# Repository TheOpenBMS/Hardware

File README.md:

# Hardware
KiCad Schematics and PCB Layout

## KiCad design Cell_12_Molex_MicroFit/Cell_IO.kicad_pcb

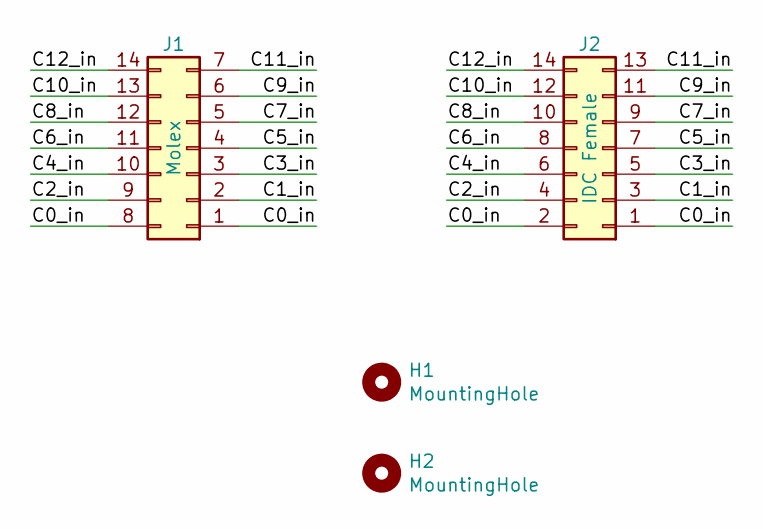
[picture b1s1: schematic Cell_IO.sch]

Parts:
H1, H2: MountingHole; MountingHole_3.2mm_M3
J1: Molex; Molex_Micro-Fit_3.0_43045-1400_2x07_P3.00mm_Horizontal
J2: IDC Female; PinSocket_2x07_P2.54mm_Horizontal

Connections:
/C0_in: J1.1, J1.8, J2.1, J2.2
/C1_in: J1.2, J2.3
/C2_in: J1.9, J2.4
/C3_in: J1.3, J2.5
/C4_in: J1.10, J2.6
/C5_in: J1.4, J2.7
/C6_in: J1.11, J2.8
/C7_in: J1.5, J2.9
/C8_in: J1.12, J2.10
/C9_in: J1.6, J2.11
/C10_in: J1.13, J2.12
/C11_in: J1.7, J2.13
/C12_in: J1.14, J2.14

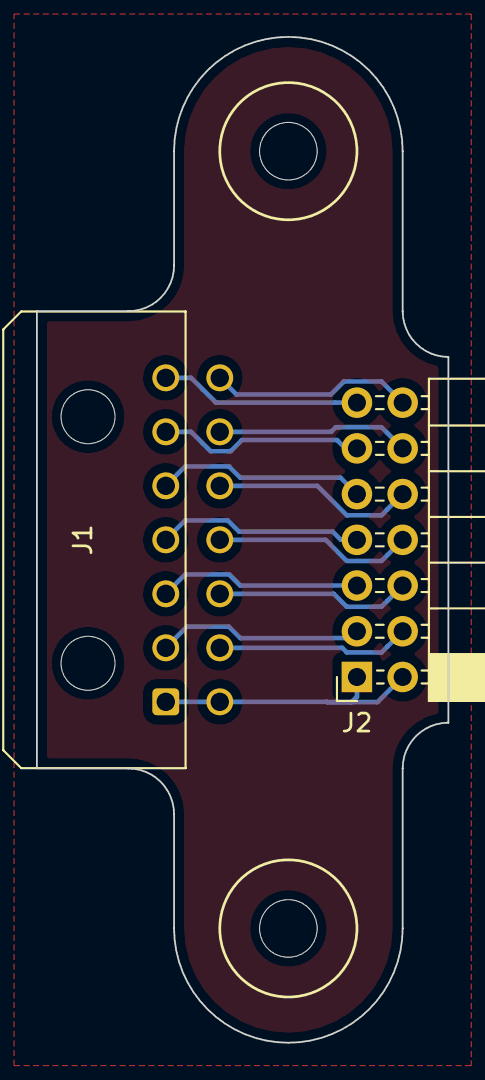
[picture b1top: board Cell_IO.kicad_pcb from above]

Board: 2 copper layers, 22.9 x 55.9 mm, 4 parts (0 on the bottom side), 13 nets.

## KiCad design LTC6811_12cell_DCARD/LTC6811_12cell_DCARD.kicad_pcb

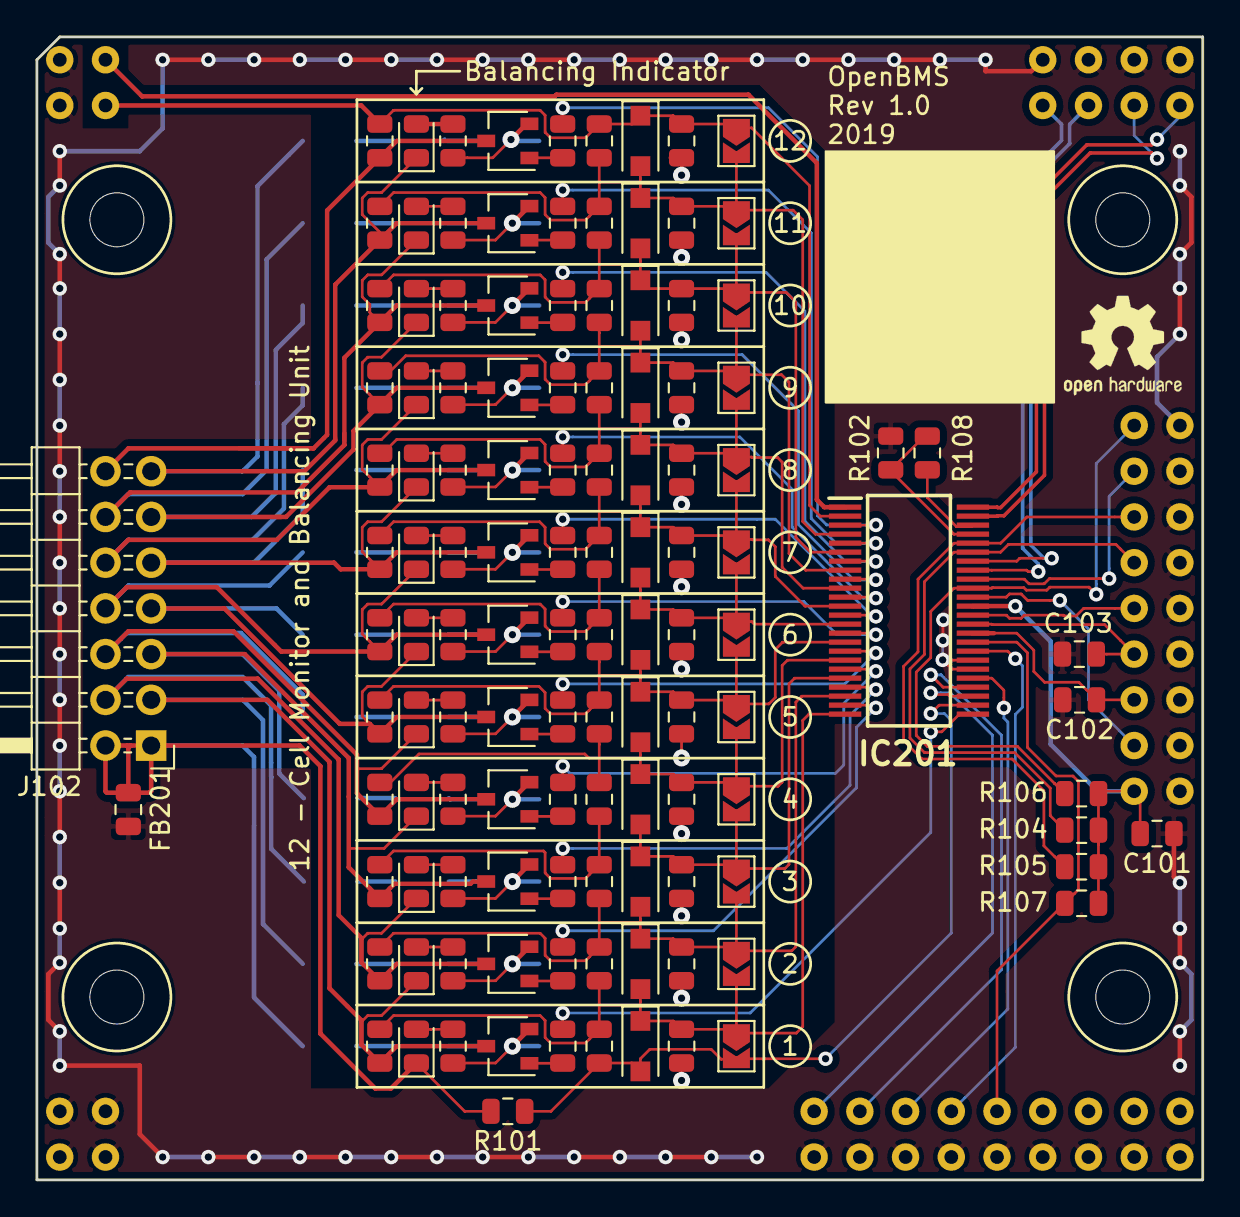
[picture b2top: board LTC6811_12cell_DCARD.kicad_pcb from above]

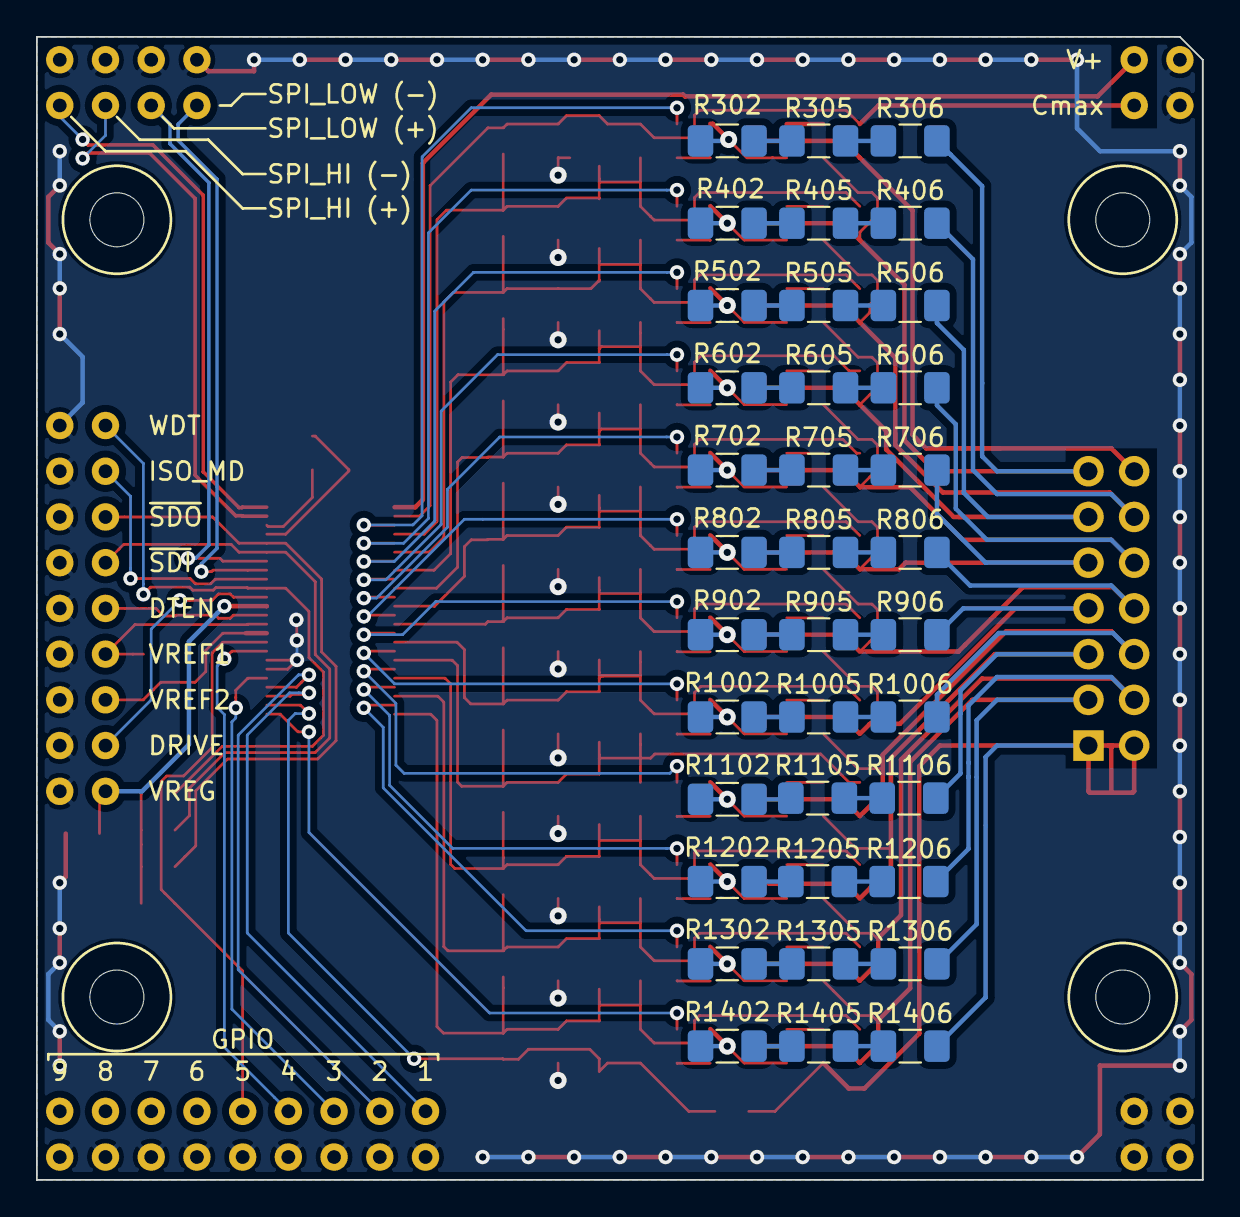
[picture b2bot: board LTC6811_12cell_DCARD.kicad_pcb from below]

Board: 2 copper layers, 64.8 x 63.5 mm, 158 parts (36 on the bottom side), 120 nets.

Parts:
C101, C102, C103: 1u; C_0805_2012Metric
C301, C401, C501, C601, C701, C801, C901, C1001, C1101, C1201, C1301, C1401: 100n; C_0805_2012Metric
C302, C402, C502, C602, C702, C802, C902, C1002, C1102, C1202, C1302, C1402: 10n; C_0805_2012Metric
D301, D401, D501, D601, D701, D801, D901, D1001, D1101, D1201, D1301, D1401: LED; LED_0805_2012Metric
D302, D402, D502, D602, D702, D802, D902, D1002, D1102, D1202, D1302, D1402: BAT46W; D_SOD-123F
FB201: Ferrite_Bead; R_0805_2012Metric
IC201: LTC6811-1; SOP50P780X200-48N
J102: Cells_1-12; PinHeader_2x07_P2.54mm_Horizontal
JP301, JP401, JP501, JP601, JP701, JP801, JP901, JP1001, JP1101, JP1201, JP1301, JP1401: Cell_Bypass; SolderJumper-2_P1.3mm_Open_TrianglePad1.0x1.5mm
Q301, Q401, Q501, Q601, Q701, Q801, Q901, Q1001, Q1101, Q1201, Q1301, Q1401: BSS308PE; SOT-23W
R101, R303, R403, R503, R603, R703, R803, R903, R1003, R1103, R1203, R1303, R1403: 100; R_0805_2012Metric
R102, R108: 1k; R_0805_2012Metric
R104, R105, R106, R107: 1M; R_0805_2012Metric
R301, R401, R501, R601, R701, R801, R901, R1001, R1101, R1201, R1301, R1401: 475; R_0805_2012Metric
R302, R305, R306, R402, R405, R406, R502, R505, R506, R602, R605, R606, R702, R705, R706, R802, R805, R806, R902, R905, R906, R1002, R1005, R1006, R1102, R1105, R1106, R1202, R1205, R1206, R1302, R1305, R1306, R1402, R1405, R1406: 11; R_1206_3216Metric_Pad1.42x1.75mm_HandSolder
R304, R404, R504, R604, R704, R804, R904, R1004, R1104, R1204, R1304, R1404: 3.3k; R_0805_2012Metric
SHD201: OpenBMS_IO

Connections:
/C0: C1402.2, D1402.2, IC201.26, JP1401.2, R101.1
/C0_in: D1401.1, FB201.1, J102.1, J102.2, R101.2, R1406.2
/C1: C1302.2, C1401.1, C1402.1, D1302.2, D1402.1, IC201.24, JP1301.2, JP1401.1, R1403.1
/C1_in: D1301.1, J102.3, Q1401.3, R1306.2, R1403.2
/C2: C1202.2, C1301.1, C1302.1, D1202.2, D1302.1, IC201.22, JP1201.2, JP1301.1, R1303.1
/C2_in: D1201.1, J102.4, Q1301.3, R1206.2, R1303.2
/C3: C1102.2, C1201.1, C1202.1, D1102.2, D1202.1, IC201.20, JP1101.2, JP1201.1, R1203.1
/C3_in: D1101.1, J102.5, Q1201.3, R1106.2, R1203.2
/C4: C1002.2, C1101.1, C1102.1, D1002.2, D1102.1, IC201.18, JP1001.2, JP1101.1, R1103.1
/C4_in: D1001.1, J102.6, Q1101.3, R1006.2, R1103.2
/C5: C902.2, C1001.1, C1002.1, D902.2, D1002.1, IC201.16, JP901.2, JP1001.1, R1003.1
/C5_in: D901.1, J102.7, Q1001.3, R906.2, R1003.2
/C6: C802.2, C901.1, C902.1, D802.2, D902.1, IC201.14, JP801.2, JP901.1, R903.1
/C6_in: D801.1, J102.8, Q901.3, R806.2, R903.2
/C7: C702.2, C801.1, C802.1, D702.2, D802.1, IC201.12, JP701.2, JP801.1, R803.1
/C7_in: D701.1, J102.9, Q801.3, R706.2, R803.2
/C8: C602.2, C701.1, C702.1, D602.2, D702.1, IC201.10, JP601.2, JP701.1, R703.1
/C8_in: D601.1, J102.10, Q701.3, R606.2, R703.2
/C9: C502.2, C601.1, C602.1, D502.2, D602.1, IC201.8, JP501.2, JP601.1, R603.1
/C9_in: D501.1, J102.11, Q601.3, R506.2, R603.2
/C10: C402.2, C501.1, C502.1, D402.2, D502.1, IC201.6, JP401.2, JP501.1, R503.1
/C10_in: D401.1, J102.12, Q501.3, R406.2, R503.2
/C11: C302.2, C401.1, C402.1, D302.2, D402.1, IC201.4, JP301.2, JP401.1, R403.1
/C11_in: D301.1, J102.13, Q401.3, R306.2, R403.2
/C12: C301.1, C302.1, D302.1, IC201.2, JP301.1, R303.1, SHD201.Cmax_in
/C12_in: J102.14, Q301.3, R303.2
/DRIVE: IC201.38, SHD201.DRIVE
/DTEN: IC201.36, SHD201.DTEN
/GPIO1: IC201.27, SHD201.GPIO1
/GPIO2: IC201.28, SHD201.GPIO2
/GPIO3: IC201.29, SHD201.GPIO3
/GPIO4: IC201.32, SHD201.GPIO4
/GPIO5: IC201.33, R107.1, SHD201.GPIO5
/IBIAS: IC201.45, R102.2, R108.1
/ICMP: IC201.46, R108.2
/IH+: IC201.48, SHD201.IHP
/IH-: IC201.47, SHD201.IHM
/IL+: IC201.42, SHD201.ILP
/IL-: IC201.41, SHD201.ILM
/ISOMD: IC201.40, SHD201.ISOMD
/S1: IC201.25, R1404.1
/S2: IC201.23, R1304.1
/S3: IC201.21, R1204.1
/S4: IC201.19, R1104.1
/S5: IC201.17, R1004.1
/S6: IC201.15, R904.1
/S7: IC201.13, R804.1
/S8: IC201.11, R704.1
/S9: IC201.9, R604.1
/S10: IC201.7, R504.1
/S11: IC201.5, R404.1
/S12: IC201.3, R304.1
/V+: IC201.1, SHD201.V+
/VREF1: C103.1, IC201.35, SHD201.VREF1
/VREF2: C102.1, IC201.34, SHD201.VREF2
/VREG: C101.1, IC201.37, R104.2, R105.2, R106.2, R107.2, SHD201.VREG
/WDT: IC201.39, R106.1, SHD201.WDT
/~SDI: IC201.43, R104.1, SHD201.~SDI
/~SDO: IC201.44, R105.1, SHD201.~SDO
GND: C101.2, C102.2, C103.2, C301.2, C401.2, C501.2, C601.2, C701.2, C801.2, C901.2, C1001.2, C1101.2, C1201.2, C1301.2, C1401.2, FB201.2, IC201.30, IC201.31, R102.1, SHD201.GND
unnamed: D301.2, R301.2
unnamed: D401.2, R401.2
unnamed: D501.2, R501.2
unnamed: D601.2, R601.2
unnamed: D701.2, R701.2
unnamed: D801.2, R801.2
unnamed: D901.2, R901.2
unnamed: D1001.2, R1001.2
unnamed: D1101.2, R1101.2
unnamed: D1201.2, R1201.2
unnamed: D1301.2, R1301.2
unnamed: D1401.2, R1401.2
unnamed: Q301.1, R304.2
unnamed: Q301.2, R301.1, R302.1
unnamed: Q401.1, R404.2
unnamed: Q401.2, R401.1, R402.1
unnamed: Q501.1, R504.2
unnamed: Q501.2, R501.1, R502.1
unnamed: Q601.1, R604.2
unnamed: Q601.2, R601.1, R602.1
unnamed: Q701.1, R704.2
unnamed: Q701.2, R701.1, R702.1
unnamed: Q801.1, R804.2
unnamed: Q801.2, R801.1, R802.1
unnamed: Q901.1, R904.2
unnamed: Q901.2, R901.1, R902.1
unnamed: Q1001.1, R1004.2
unnamed: Q1001.2, R1001.1, R1002.1
unnamed: Q1101.1, R1104.2
unnamed: Q1101.2, R1101.1, R1102.1
unnamed: Q1201.1, R1204.2
unnamed: Q1201.2, R1201.1, R1202.1
unnamed: Q1301.1, R1304.2
unnamed: Q1301.2, R1301.1, R1302.1
unnamed: Q1401.1, R1404.2
unnamed: Q1401.2, R1401.1, R1402.1
unnamed: R302.2, R305.1
unnamed: R305.2, R306.1
unnamed: R402.2, R405.1
unnamed: R405.2, R406.1
unnamed: R502.2, R505.1
unnamed: R505.2, R506.1
unnamed: R602.2, R605.1
unnamed: R605.2, R606.1
unnamed: R702.2, R705.1
unnamed: R705.2, R706.1
unnamed: R802.2, R805.1
unnamed: R805.2, R806.1
unnamed: R902.2, R905.1
unnamed: R905.2, R906.1
unnamed: R1002.2, R1005.1
unnamed: R1005.2, R1006.1
unnamed: R1102.2, R1105.1
unnamed: R1105.2, R1106.1
unnamed: R1202.2, R1205.1
unnamed: R1205.2, R1206.1
unnamed: R1302.2, R1305.1
unnamed: R1305.2, R1306.1
unnamed: R1402.2, R1405.1
unnamed: R1405.2, R1406.1

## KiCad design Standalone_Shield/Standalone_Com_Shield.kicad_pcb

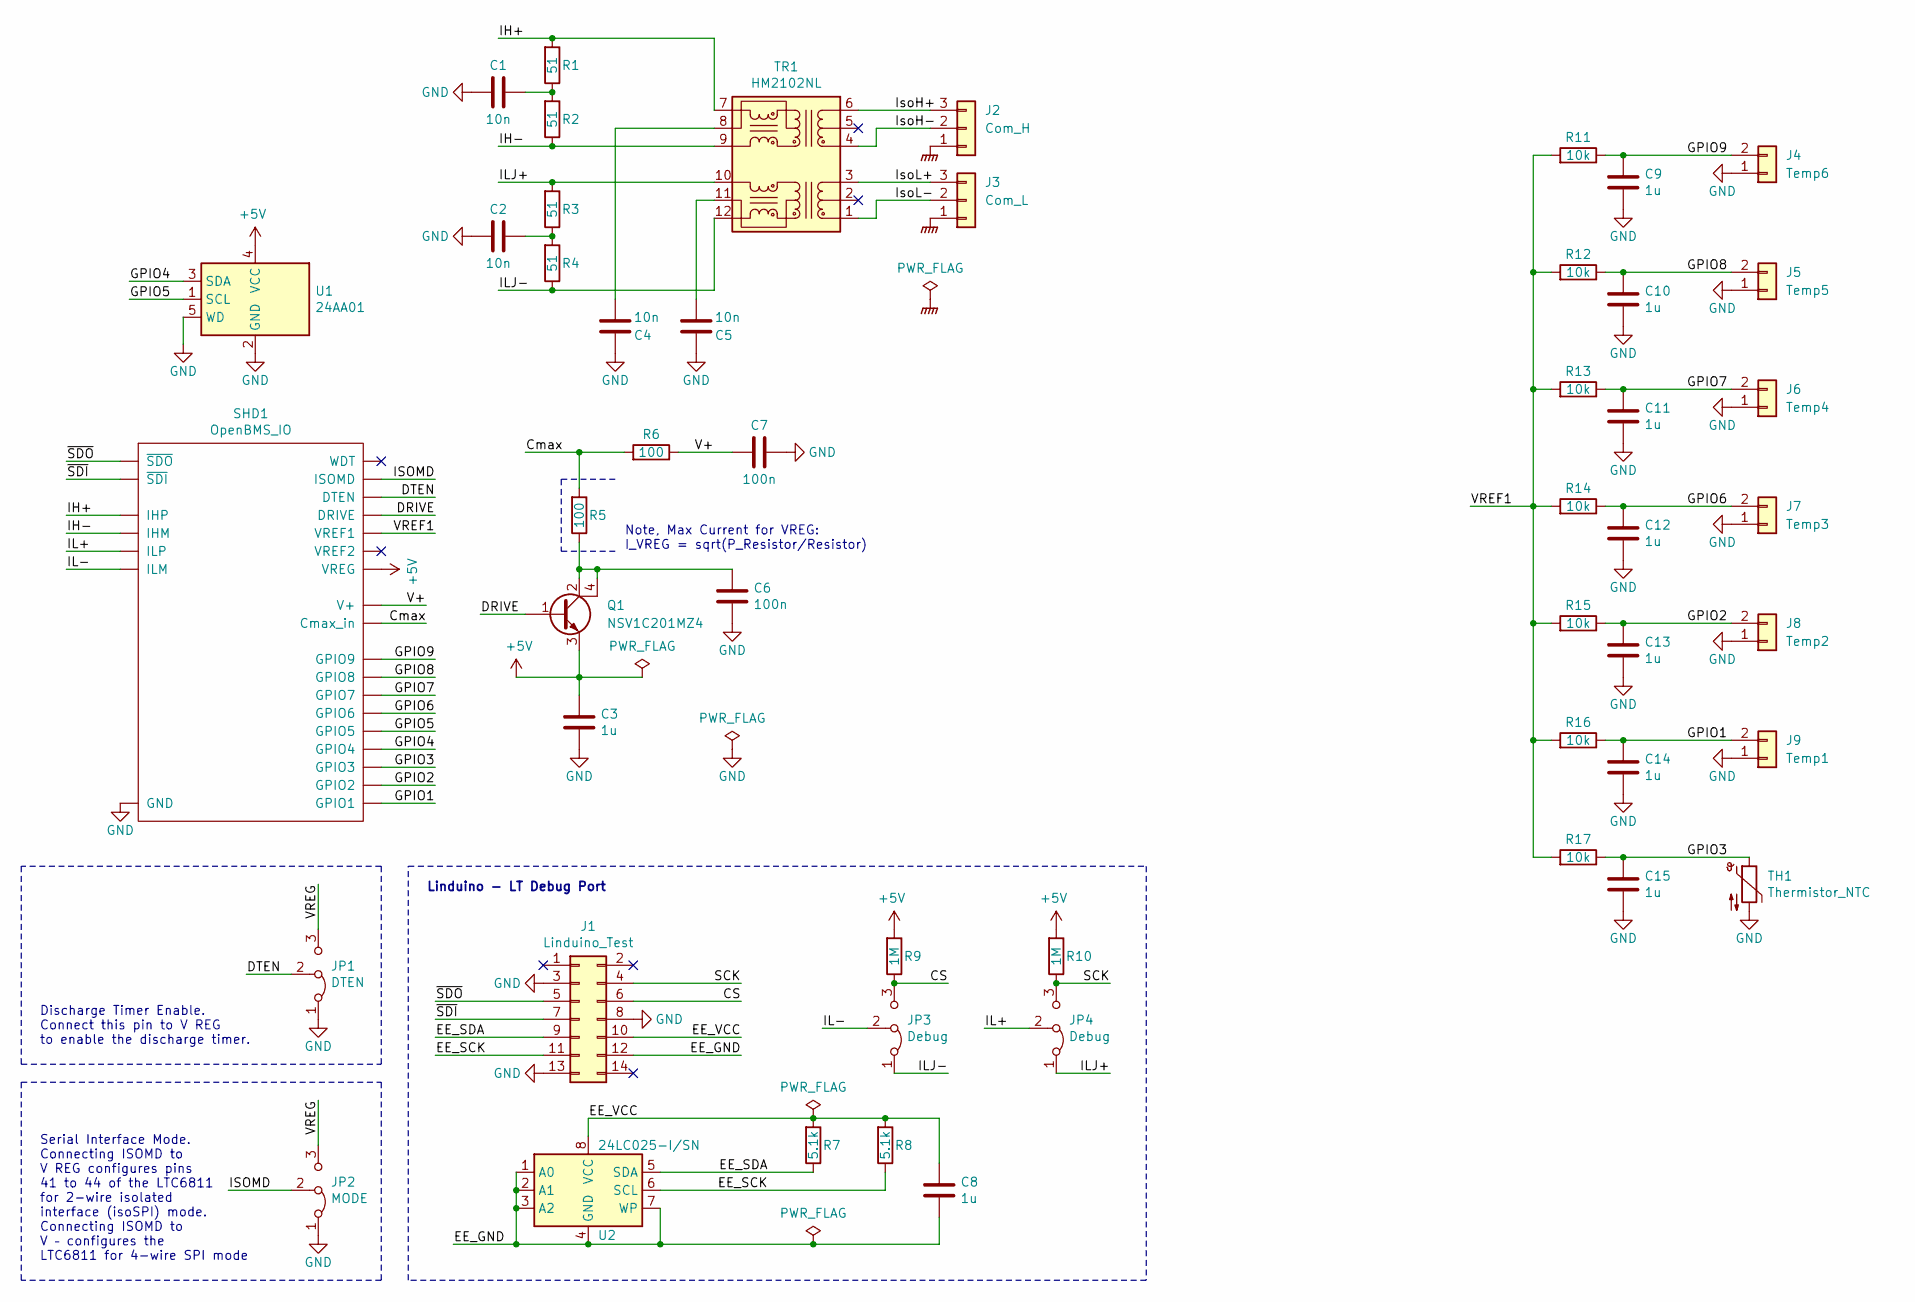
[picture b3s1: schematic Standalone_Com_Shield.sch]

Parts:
C1, C2, C4, C5: 10n; C_0805_2012Metric
C3, C8, C9, C10, C11, C12, C13, C14, C15: 1u; C_0805_2012Metric
C6, C7: 100n; C_0805_2012Metric
J1: Linduino_Test; IDC-Header_2x07_P2.54mm_Vertical
J2: Com_H; JST_XH_S03B-XH-A_1x03_P2.50mm_Horizontal
J3: Com_L; JST_XH_S03B-XH-A_1x03_P2.50mm_Horizontal
J4: Temp6; JST_PH_B2B-PH-SM4-TB_1x02-1MP_P2.00mm_Vertical
J5: Temp5; JST_PH_B2B-PH-SM4-TB_1x02-1MP_P2.00mm_Vertical
J6: Temp4; JST_PH_B2B-PH-SM4-TB_1x02-1MP_P2.00mm_Vertical
J7: Temp3; JST_PH_B2B-PH-SM4-TB_1x02-1MP_P2.00mm_Vertical
J8: Temp2; JST_PH_B2B-PH-SM4-TB_1x02-1MP_P2.00mm_Vertical
J9: Temp1; JST_PH_B2B-PH-SM4-TB_1x02-1MP_P2.00mm_Vertical
JP1: DTEN; PinHeader_1x03_P2.54mm_Horizontal
JP2: MODE; PinHeader_1x03_P2.54mm_Horizontal
JP3, JP4: Debug; PinHeader_1x03_P2.54mm_Horizontal
Q1: NSV1C201MZ4; SOT-223
R1, R2, R3, R4: 51; R_0805_2012Metric
R5, R6: 100; R_0805_2012Metric
R7, R8: 5.1k; R_0805_2012Metric
R9, R10: 1M; R_0805_2012Metric
R11, R12, R13, R14, R15, R16, R17: 10k; R_0805_2012Metric
SHD1: OpenBMS_IO
TH1: Thermistor_NTC; R_0603_1608Metric
TR1: HM2102NL
U1: 24AA01; SOT-23-5
U2: 24LC025-I/SN; SOIC-8_3.9x4.9mm_P1.27mm

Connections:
+5V: C3.1, Q1.3 (E), R9.2, R10.2, SHD1.VREG, U1.4 (VCC)
/CS: J1.6, JP3.3 (B), R9.1
/Cmax: R5.2, R6.2, SHD1.Cmax_in
/DRIVE: Q1.1 (B), SHD1.DRIVE
/DTEN: JP1.2 (C), SHD1.DTEN
/EE_GND: C8.2, J1.12, U2.1 (A0), U2.2 (A1), U2.3 (A2), U2.4 (GND), U2.7 (WP)
/EE_SCK: J1.11, R8.1, U2.6 (SCL)
/EE_SDA: J1.9, R7.1, U2.5 (SDA)
/EE_VCC: C8.1, J1.10, R7.2, R8.2, U2.8 (VCC)
/GPIO1: C14.1, J9.2, R16.1, SHD1.GPIO1
/GPIO2: C13.1, J8.2, R15.1, SHD1.GPIO2
/GPIO3: C15.1, R17.1, SHD1.GPIO3, TH1.1
/GPIO4: SHD1.GPIO4, U1.3 (SDA)
/GPIO5: SHD1.GPIO5, U1.1 (SCL)
/GPIO6: C12.1, J7.2, R14.1, SHD1.GPIO6
/GPIO7: C11.1, J6.2, R13.1, SHD1.GPIO7
/GPIO8: C10.1, J5.2, R12.1, SHD1.GPIO8
/GPIO9: C9.1, J4.2, R11.1, SHD1.GPIO9
/IH+: R1.2, SHD1.IHP, TR1.7 (RX-)
/IH-: R2.1, SHD1.IHM, TR1.9 (RX+)
/IL+: JP4.2 (C), SHD1.ILP
/IL-: JP3.2 (C), SHD1.ILM
/ILJ+: JP4.1 (A), R3.2, TR1.10 (TX-)
/ILJ-: JP3.1 (A), R4.1, TR1.12 (TX+)
/ISOMD: JP2.2 (C), SHD1.ISOMD
/IsoH+: J2.3, TR1.6 (RD-)
/IsoH-: J2.2, TR1.4 (RD+)
/IsoL+: J3.3, TR1.3 (TD-)
/IsoL-: J3.2, TR1.1 (TD+)
/SCK: J1.4, JP4.3 (B), R10.1
/V+: C7.1, R6.1, SHD1.V+
/VREF1: R11.2, R12.2, R13.2, R14.2, R15.2, R16.2, R17.2, SHD1.VREF1
/VREG: JP1.3 (B), JP2.3 (B)
/~SDI: J1.7, SHD1.~SDI
/~SDO: J1.5, SHD1.~SDO
GND: C1.2, C2.2, C3.2, C4.2, C5.2, C6.2, C7.2, C9.2, C10.2, C11.2, C12.2, C13.2, C14.2, C15.2, J1.3, J1.8, J1.13, J4.1, J5.1, J6.1, J7.1, J8.1, J9.1, JP1.1 (A), JP2.1 (A), SHD1.GND, TH1.2, U1.2 (GND), U1.5 (WD)
GNDPWR: J2.1, J3.1
unnamed: C1.1, R1.1, R2.2
unnamed: C2.1, R3.1, R4.2
unnamed: C4.1, TR1.8 (C_RX)
unnamed: C5.1, TR1.11 (C_TX)
unnamed: C6.1, Q1.2 (C), Q1.4 (C), R5.1

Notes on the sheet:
Note, Max Current for VREG: I_VREG = sqrt(P_Resistor/Resistor)
Serial Interface Mode. Connecting ISOMD to V REG configures pins 41 to 44 of the LTC6811 for 2-wire isolated interface (isoSPI) mode. Connecting ISOMD to V – configures the LTC6811 for 4-wire SPI mode
Discharge Timer Enable. Connect this pin to V REG to enable the discharge timer.
Linduino - LT Debug Port

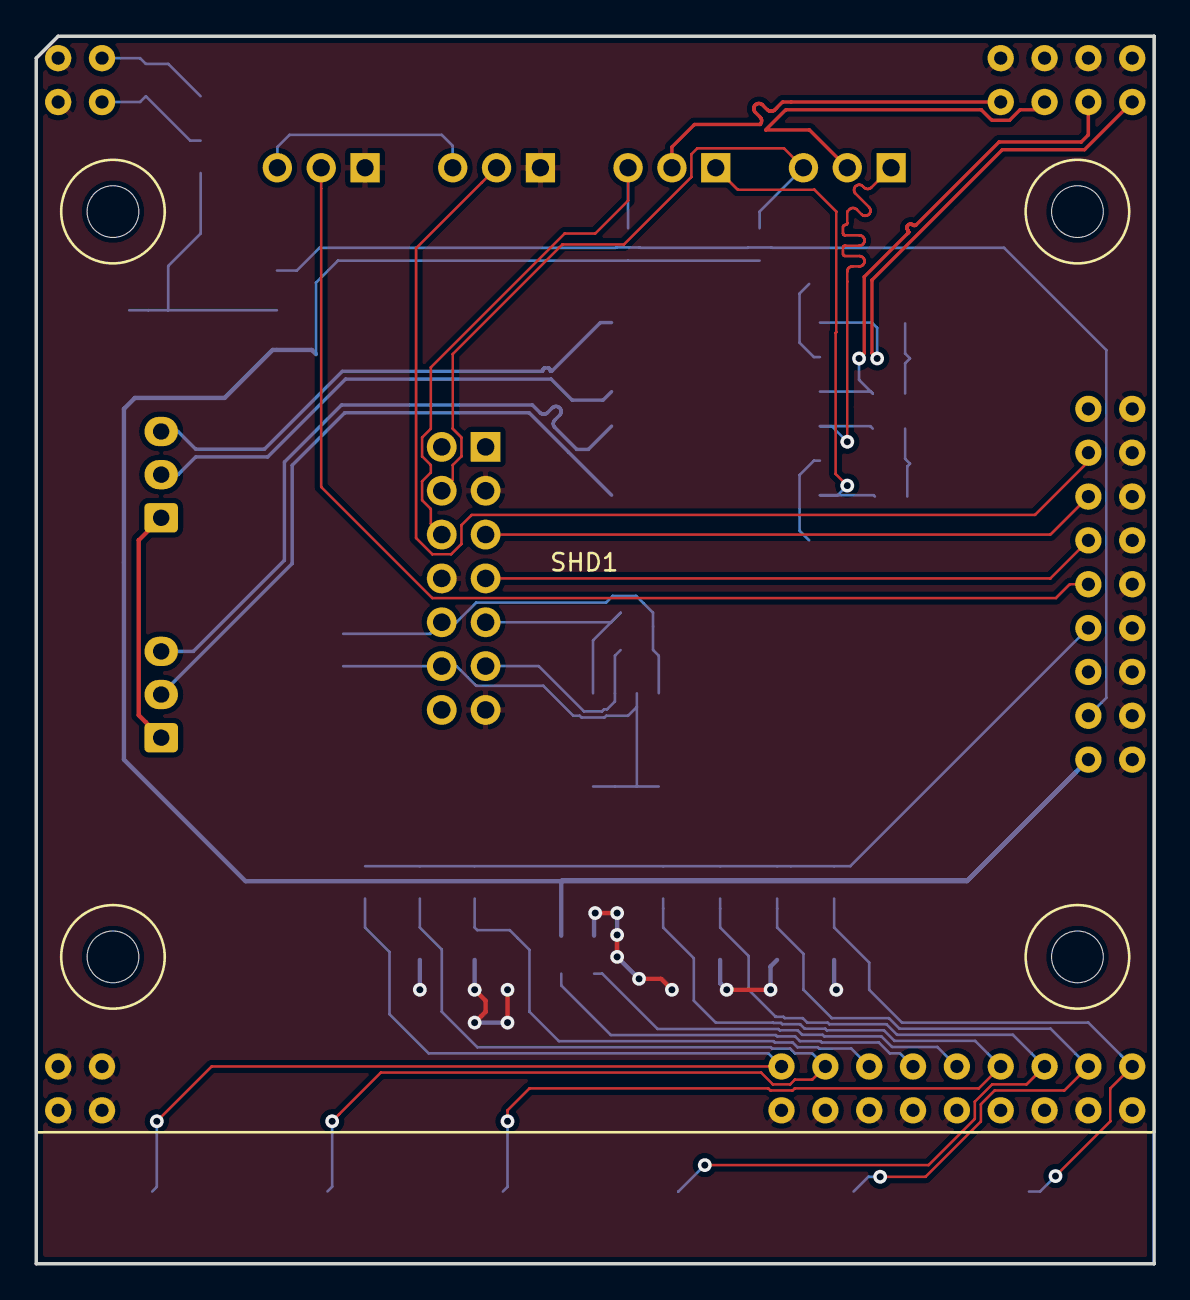
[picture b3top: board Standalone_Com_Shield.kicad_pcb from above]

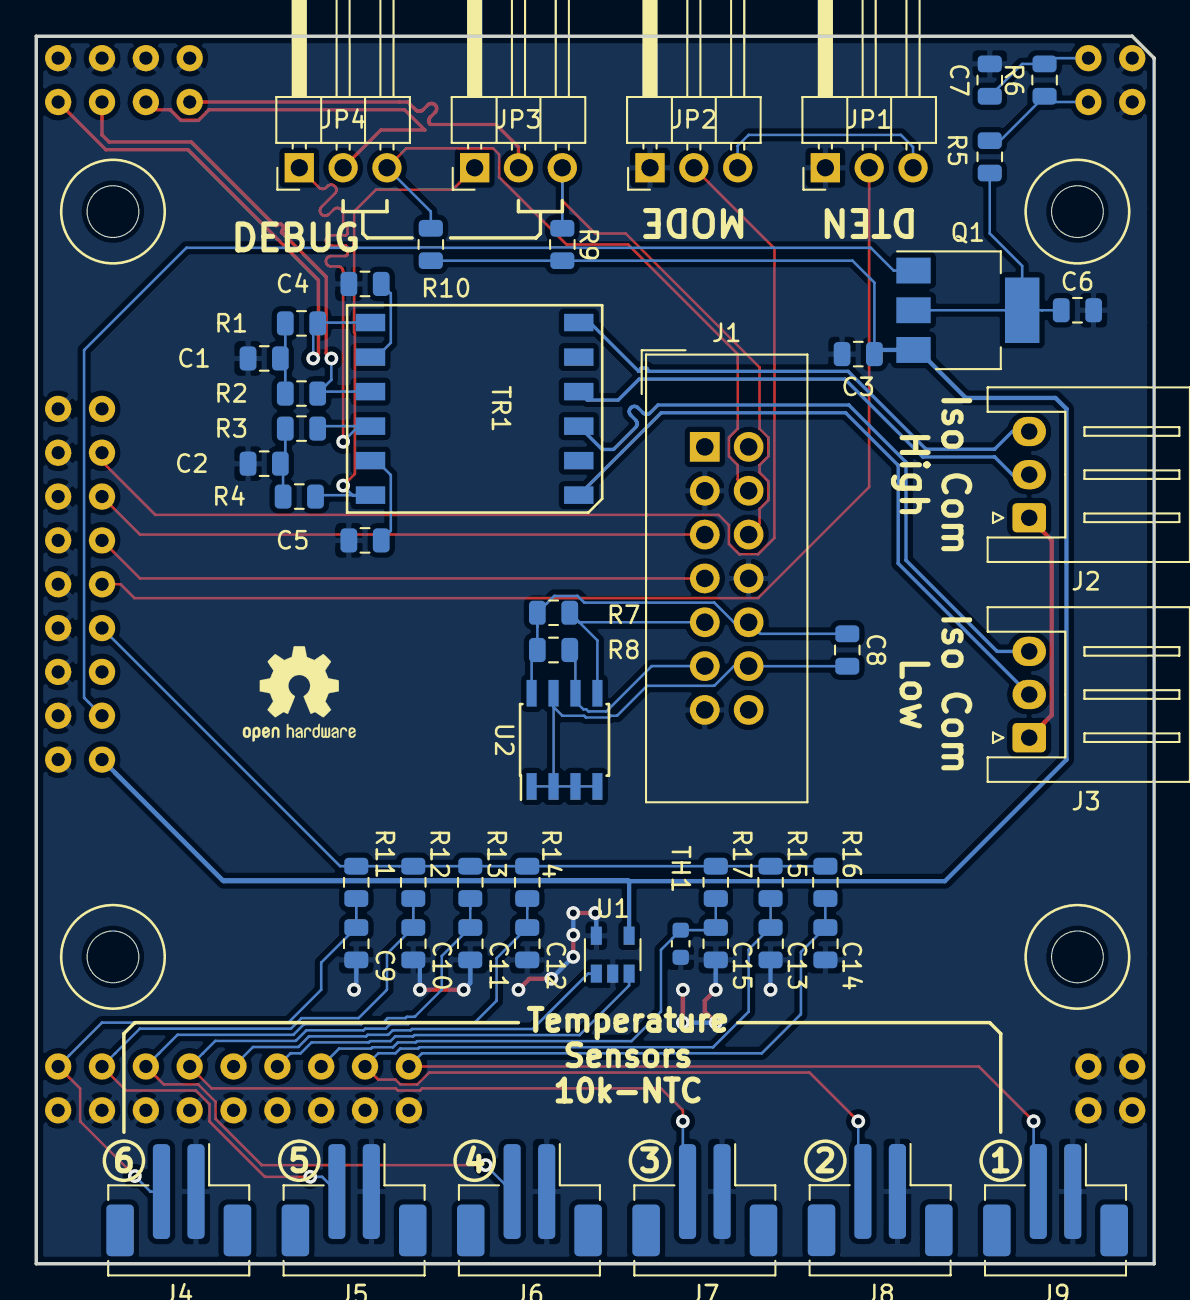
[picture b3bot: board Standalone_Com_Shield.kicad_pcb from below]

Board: 2 copper layers, 64.8 x 71.1 mm, 51 parts (50 on the bottom side), 42 nets.

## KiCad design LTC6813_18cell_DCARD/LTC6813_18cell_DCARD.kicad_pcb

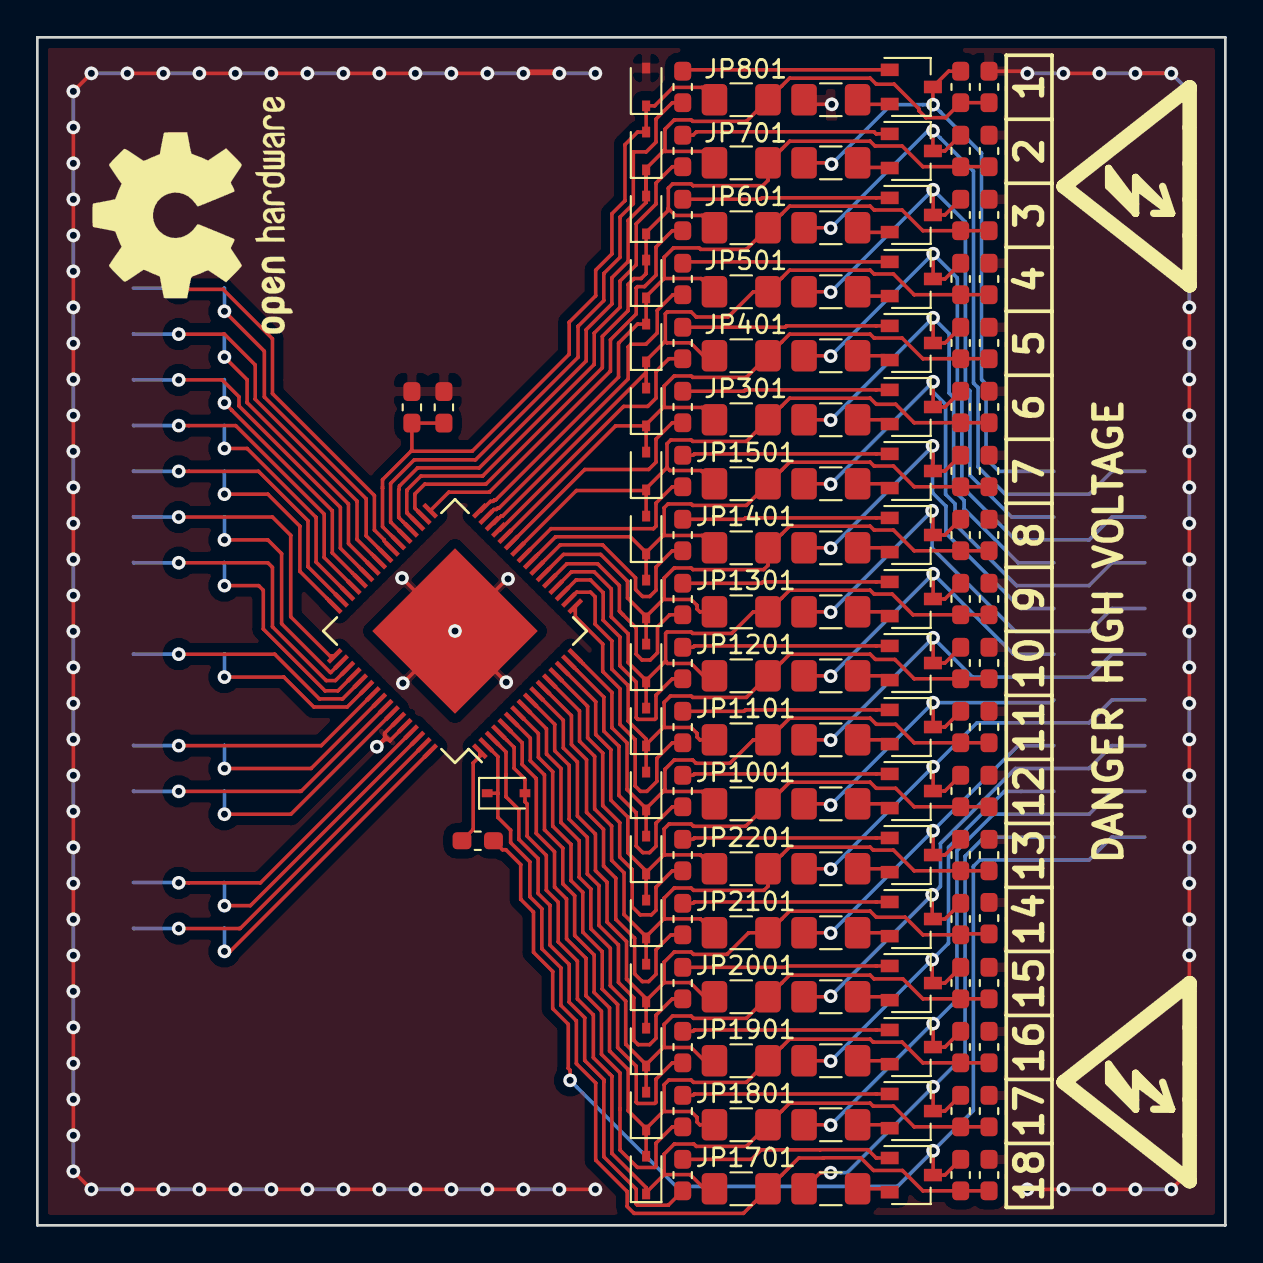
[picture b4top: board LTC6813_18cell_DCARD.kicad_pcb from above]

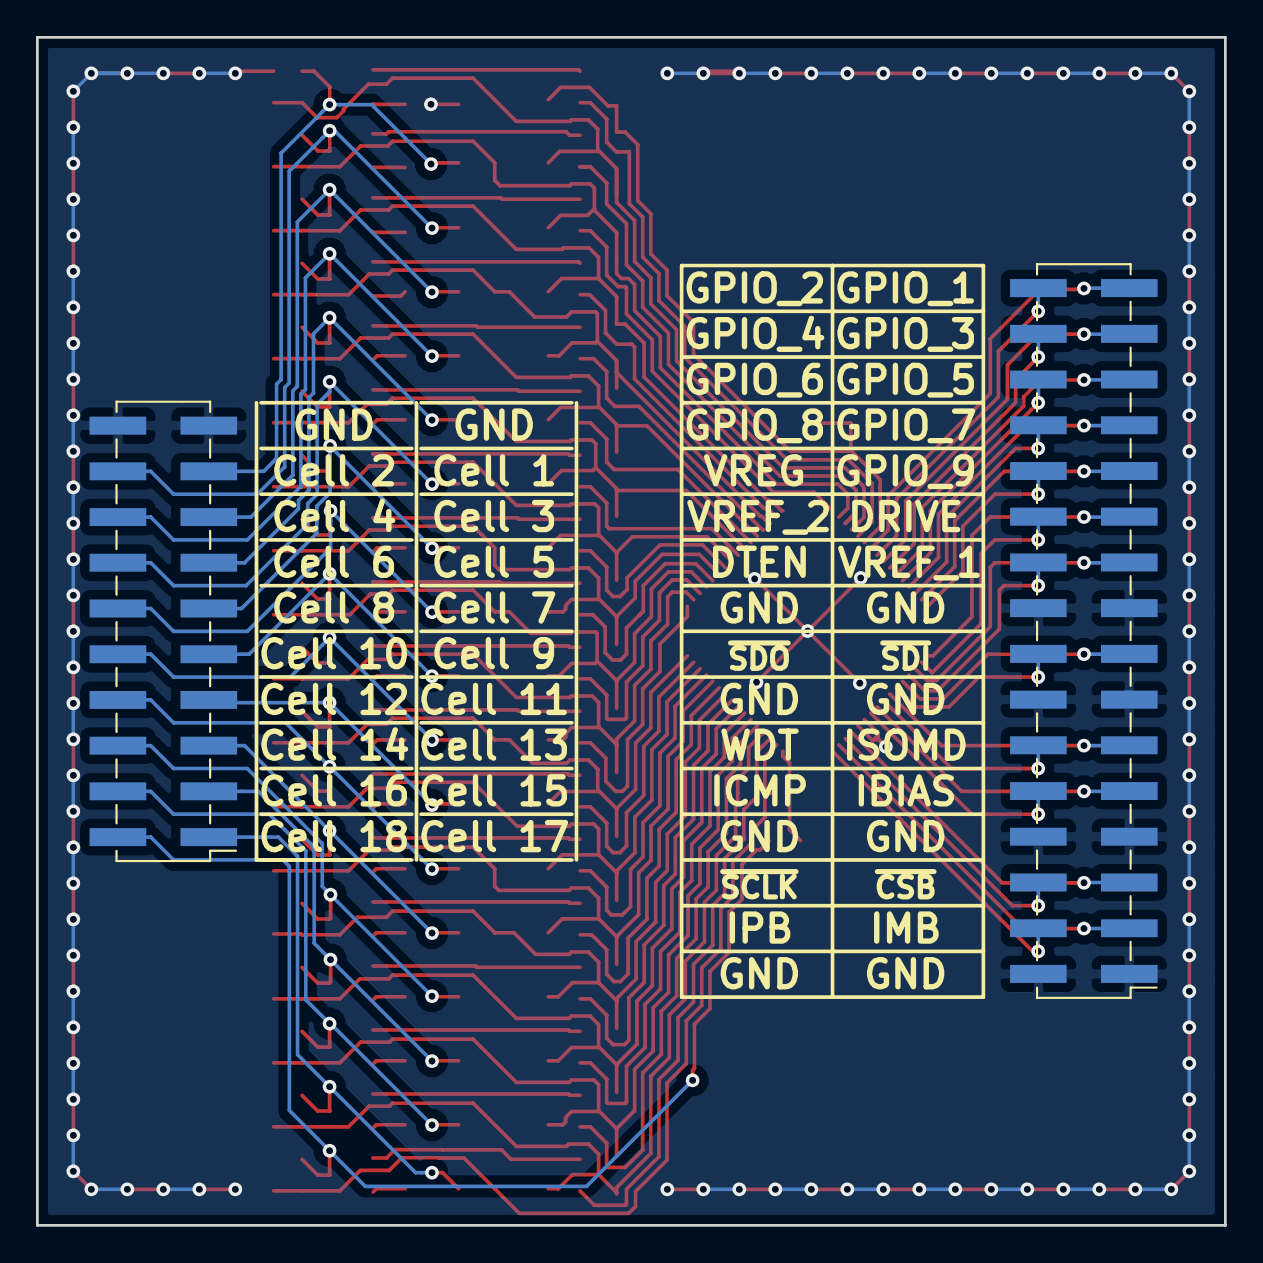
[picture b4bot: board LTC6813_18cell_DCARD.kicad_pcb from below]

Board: 2 copper layers, 66.0 x 66.0 mm, 133 parts (2 on the bottom side), 117 nets.

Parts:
C101, C301, C401, C501, C601, C701, C801, C1001, C1101, C1201, C1301, C1401, C1501, C1701, C1801, C1901, C2001, C2101, C2201: 100n; C_0603_1608Metric_Pad1.05x0.95mm_HandSolder
D101: D_Zener_ALT; D_SOD-323
D301, D401, D501, D601, D701, D801, D1001, D1101, D1201, D1301, D1401, D1501, D1701, D1801, D1901, D2001, D2101, D2201: Zener_6.8V; D_SOD-323
IC101: LTC6813ILWE-1#3ZZPBF; LQFP-64-1EP_10x10mm_P0.5mm_EP6.5x6.5mm
J101: Conn_02x16_Counter_Clockwise; PinHeader_2x16_P2.54mm_Vertical_SMD
J102: Conn_02x10_Counter_Clockwise; PinHeader_2x10_P2.54mm_Vertical_SMD
JP301, JP401, JP501, JP601, JP701, JP801, JP1001, JP1101, JP1201, JP1301, JP1401, JP1501, JP1701, JP1801, JP1901, JP2001, JP2101, JP2201: Cell_Bypass; R_1206_3216Metric_Pad1.42x1.75mm_HandSolder
Q301, Q401, Q501, Q601, Q701, Q801, Q1001, Q1101, Q1201, Q1301, Q1401, Q1501, Q1701, Q1801, Q1901, Q2001, Q2101, Q2201: BSS308PE; SOT-23W
R101, R102, R302, R402, R502, R602, R702, R802, R1002, R1102, R1202, R1302, R1402, R1502, R1702, R1802, R1902, R2002, R2102, R2202: 100; R_0603_1608Metric_Pad1.05x0.95mm_HandSolder
R301, R401, R501, R601, R701, R801, R1001, R1101, R1201, R1301, R1401, R1501, R1701, R1801, R1901, R2001, R2101, R2201: 33; R_1206_3216Metric_Pad1.42x1.75mm_HandSolder
R303, R403, R503, R603, R703, R803, R1003, R1103, R1203, R1303, R1403, R1503, R1703, R1803, R1903, R2003, R2103, R2203: 3.3k; R_0603_1608Metric_Pad1.05x0.95mm_HandSolder

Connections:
C0: C101.1, D101.1, D801.2, IC101.38, JP801.2, R101.1
C1: C801.1, D701.2, D801.1, IC101.36, JP701.2, JP801.1, R802.1
C1_in: J102.17, Q801.3, R701.2, R802.2
C2: C701.1, D601.2, D701.1, IC101.34, JP601.2, JP701.1, R702.1
C2_in: J102.18, Q701.3, R601.2, R702.2
C3: C601.1, D501.2, D601.1, IC101.32, JP501.2, JP601.1, R602.1
C3_in: J102.15, Q601.3, R501.2, R602.2
C4: C501.1, D401.2, D501.1, IC101.30, JP401.2, JP501.1, R502.1
C4_in: J102.16, Q501.3, R401.2, R502.2
C5: C401.1, D301.2, D401.1, IC101.28, JP301.2, JP401.1, R402.1
C5_in: J102.13, Q401.3, R301.2, R402.2
C6: C301.1, D301.1, D1501.2, IC101.26, JP301.1, JP1501.2, R302.1
C6_in: J102.14, Q301.3, R302.2, R1501.2
C7: C1501.1, D1401.2, D1501.1, IC101.24, JP1401.2, JP1501.1, R1502.1
C7_in: J102.11, Q1501.3, R1401.2, R1502.2
C8: C1401.1, D1301.2, D1401.1, IC101.22, JP1301.2, JP1401.1, R1402.1
C8_in: J102.12, Q1401.3, R1301.2, R1402.2
C9: C1301.1, D1201.2, D1301.1, IC101.20, JP1201.2, JP1301.1, R1302.1
C9_in: J102.9, Q1301.3, R1201.2, R1302.2
C10: C1201.1, D1101.2, D1201.1, IC101.18, JP1101.2, JP1201.1, R1202.1
C10_in: J102.10, Q1201.3, R1101.2, R1202.2
C11: C1101.1, D1001.2, D1101.1, IC101.16, JP1001.2, JP1101.1, R1102.1
C11_in: J102.7, Q1101.3, R1001.2, R1102.2
C12: C1001.1, D1001.1, D2201.2, IC101.14, JP1001.1, JP2201.2, R1002.1
C12_in: J102.8, Q1001.3, R1002.2, R2201.2
C13: C2201.1, D2101.2, D2201.1, IC101.12, JP2101.2, JP2201.1, R2202.1
C13_in: J102.5, Q2201.3, R2101.2, R2202.2
C14: C2101.1, D2001.2, D2101.1, IC101.10, JP2001.2, JP2101.1, R2102.1
C14_in: J102.6, Q2101.3, R2001.2, R2102.2
C15: C2001.1, D1901.2, D2001.1, IC101.8, JP1901.2, JP2001.1, R2002.1
C15_in: J102.3, Q2001.3, R1901.2, R2002.2
C16: C1901.1, D1801.2, D1901.1, IC101.6, JP1801.2, JP1901.1, R1902.1
C16_in: J102.4, Q1901.3, R1801.2, R1902.2
C17: C1801.1, D1701.2, D1801.1, IC101.4, JP1701.2, JP1801.1, R1802.1
C17_in: J102.1, Q1801.3, R1701.2, R1802.2
C18: C1701.1, D1701.1, IC101.2, JP1701.1, R1702.1
C18_in: J102.2, Q1701.3, R102.2, R1702.2
DRIVE: IC101.49, J101.21
DTEN: IC101.52, J101.20
GND: C101.2, C301.2, C401.2, C501.2, C601.2, C701.2, C801.2, C1001.2, C1101.2, C1201.2, C1301.2, C1401.2, C1501.2, C1701.2, C1801.2, C1901.2, C2001.2, C2101.2, C2201.2, D101.2, IC101.59, IC101.60, IC101.65, J101.1, J101.2, J101.7, J101.8, J101.13, J101.14, J101.17, J101.18, J102.19, J102.20, R101.2, R801.2
GPIO1: IC101.39, J101.31
GPIO2: IC101.40, J101.32
GPIO3: IC101.41, J101.29
GPIO4: IC101.42, J101.30
GPIO5: IC101.43, J101.27
GPIO6: IC101.44, J101.28
GPIO7: IC101.45, J101.25
GPIO8: IC101.46, J101.26
GPIO9: IC101.47, J101.23
IBIAS: IC101.57, J101.9
ICMP: IC101.58, J101.10
IMB: IC101.63, J101.3
IPB: IC101.64, J101.4
ISOMD: IC101.55, J101.11
unnamed: IC101.1, R102.1
unnamed: Q301.1, R303.2
unnamed: Q301.2, R301.1
unnamed: Q401.1, R403.2
unnamed: Q401.2, R401.1
unnamed: Q501.1, R503.2
unnamed: Q501.2, R501.1
unnamed: Q601.1, R603.2
unnamed: Q601.2, R601.1
unnamed: Q701.1, R703.2
unnamed: Q701.2, R701.1
unnamed: Q801.1, R803.2
unnamed: Q801.2, R801.1
unnamed: Q1001.1, R1003.2
unnamed: Q1001.2, R1001.1
unnamed: Q1101.1, R1103.2
unnamed: Q1101.2, R1101.1
unnamed: Q1201.1, R1203.2
unnamed: Q1201.2, R1201.1
unnamed: Q1301.1, R1303.2
unnamed: Q1301.2, R1301.1
unnamed: Q1401.1, R1403.2
unnamed: Q1401.2, R1401.1
unnamed: Q1501.1, R1503.2
unnamed: Q1501.2, R1501.1
unnamed: Q1701.1, R1703.2
unnamed: Q1701.2, R1701.1
unnamed: Q1801.1, R1803.2
unnamed: Q1801.2, R1801.1
unnamed: Q1901.1, R1903.2
unnamed: Q1901.2, R1901.1
unnamed: Q2001.1, R2003.2
unnamed: Q2001.2, R2001.1
unnamed: Q2101.1, R2103.2
unnamed: Q2101.2, R2101.1
unnamed: Q2201.1, R2203.2
unnamed: Q2201.2, R2201.1
S1: IC101.37, R803.1
S2: IC101.35, R703.1
S3: IC101.33, R603.1
S4: IC101.31, R503.1
S5: IC101.29, R403.1
S6: IC101.27, R303.1
S7: IC101.25, R1503.1
S8: IC101.23, R1403.1
S9: IC101.21, R1303.1
S10: IC101.19, R1203.1
S11: IC101.17, R1103.1
S12: IC101.15, R1003.1
S13: IC101.13, R2203.1
S14: IC101.11, R2103.1
S15: IC101.9, R2003.1
S16: IC101.7, R1903.1
S17: IC101.5, R1803.1
S18: IC101.3, R1703.1
VREF1: IC101.51, J101.19
VREF2: IC101.50, J101.22
VREG: IC101.48, J101.24
WDT: IC101.56, J101.12
~CSB: IC101.61, J101.5
~SCLK: IC101.62, J101.6
~SDI: IC101.53, J101.15
~SDO: IC101.54, J101.16
